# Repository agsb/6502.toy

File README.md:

# A 6502 toy

(this file is a stub)

## Introduction

_I seek for learn, not for speed._

I had an Apple II. The Furby was a two 6502 'like' toy. 

I want make a ~SBC minimal~ as my toy.

We know the Terminator’s main CPU is a 6502.

There are many "clones" [Ben Eater](https://eater.net/6502), [Mike](https://github.com/mike42/6502-computer), [Maarten](https://github.com/maarten-pennings/6502/tree/master), [Grant](http://searle.x10host.com/6502/Simple6502.html), [Álvarez](https://www.ele.uva.es/~jesus/6502copy/proto.html) and others.

And a Great support from [6502.org](http://6502.org/) forum and [Wilson Mines Co](http://wilsonminesco.com/).

This is a board for learn and testing the version for 6502 of Minimal Indirect Thread Code Forth as [IMMU](https://github.com/agsb/immu)

PS.

- [Ben Eater](https://www.youtube.com/watch?v=LnzuMJLZRdU) made a revival of 6502. 
- using ROM, for read-only memory, never changes
- using RAM, for random access memory, ever changes
- using REM, for regular eeprom memory, can changes (I2C, SPI, etc)
        
## Road Map

- make all circuit plans (W.I.P.)
- make a eeprom programmer like [Ben Eater](https://github.com/beneater/eeprom-programmer), but using arduino nano and some change in pins used.
- make a nop circuit to test cpus, using a arduino mini and [clockvar6502](https://github.com/maarten-pennings/6502/blob/master/1clock/clockvar6502)
- wire wrap the boards
          
## Hardware

### B.O.M

        - 01 x NMOS 6502 (or CMOS 65C02),
        - 01 x AT28C64, 8kb EEPROM
        - 02 x HM62256, 32kb SRAM

        - 01 x CMOS 6522, VIA Interface
        - 01 x CMOS 6551, CIA Interface

        - 02 x 74HC00, 4x2 NAND
        - 01 x 74HC04, 6x NOT
        - 01 x 74HC27, 3x3 NOR
        - 01 x 74HC10, 3x3 NAND
        - 01 x 74HC74, 2x D-FlipFlop
        - 01 x 74HC138, 3:8 DeMux

        - 08 x 3k3 Ohm, common pull-up
        - 08 x 10k0 Ohm,  weak pull-up
        - n x  0.1 uF, decoupling
        - 02 x 4.7 uF, buffer
        - 01 x crystal 1.8432 MHz,
        - 01 x  TS1813, reset delay

        - n  x color leds,
        - n  x small resistors,

        - 02 x AT24LC512, 64kb I2C EEPROM

## Topics

The 6502's default frequency of about 1 MHz is merely illustrative compared to the 3.6 GHz of current CPUs.
   
The USART is at 9600/19200 bps, 8-N-1, duplex. 

The I2C EEPROM used as permanent storage, 1 kb blocks, 64 bytes screens.
        
All devices are CMOS and 5V capable.        

Use wire wrap. 

Test NMOS-6502, CMOS-65C02,

The actual memory map will be 56k SRAM $0000-$DFFF, 8k EEPROM $E000-$FFFF and $FE00-$FEFF 256b for devices. 

The devices are mapped at $FE00 to $FEFF, reserving 16 bytes for control for each of 16 devices.

The board will have one 6551 ACIA and one (two?) 6522 VIA inside, with expansion of more devices.

Also using a 3:8 74HC138 decoder, with $0 reserved, $1 ACIA, $2 VIA, $3 VIA reserved, onboard and $4 to $7 for expansion.

A clock board by crystal of 1.8432 MHz for CIA and by 74HC74 of 0.9612 MHz for CPU.

A beat tick as NMI with 10ms delay using VIA T1 timer.

No VGA video or 101 keyboard, using terminal at USART 9600/19200 8N1, RS-232, vt-100. 

Using a LCD 16x4 by I2C, a keyboard with 6/12 keys, a beeper, a speaker and a pool of leds, for minimal use.

Using I2C and SPI protocols and devices. 

The board have two extra 8-pins DIPs slots for I2C epproms.

Use MicroChip [AARDVARK](https://onlinedocs.microchip.com/oxy/GUID-A21CD3C1-401E-4D3B-A45B-78E60737CD44-en-US-8/GUID-92136A89-CE06-46A2-8F03-80317EDD4F89.html) connector, for interface I2C and SPI

Use [UEXT](https://en.wikipedia.org/wiki/UEXT) interface for USART, I2C, SPI, 3V3, 5V0, GND

Use [65SIB](http://forum.6502.org/viewtopic.php?t=1064&start=105) for alternative interface.

Use a 64 pin connector for expansion modules.

## Software

At boot BIOS does have all functions and loads a monitor to RAM, or 

At boot, the bios will copy bytes from a I2C eeprom into RAM and jump to it.

Use a BIOS and Forth, 

Use USART for VT100 terminal, FDDI/USB for Tera-Term or PuTTy at a computer.

### Bios

Consider ram is static random memory, rom is eeprom memory and rem is flash memory

generic routines at bios:

    - ram2ram, copy bytes from RAM to RAM
    - rem2ram, copy bytes from REM to RAM
    - ram2rem, copy bytes from RAM to REM
    
    - set_spi, prepare spi
    - set_i2c, prepare i2c
    - set_sram, prepare sram page
    
    - getc, uart get a char 
    - putc, uart put a char
    
    - getcq, verify to get
    - putcq, verify to put
    
    - getp, generic port get
    - putp, generic port put
    
    - beep, as is
    - tone, play a tone
    
    - tick_put, write into counter
    - tick_get, read from counter
    - tick_run, starts counter
    - tick_hlt, stops counter
    
    - roulette, random number from 0 to 36
    - seed, random seed from 0 to $FFFF
    - random, returns a random number from 0 to $FF

    - hex2bin, convert a hexagesimal ascii to byte ($00 to $FF)
    - bin2hex, convert a byte to hexagesimal ascii ($00 to $FF)
    
## Memory 

The first 4k of RAM $0000-$0FFF is reserved for system.

The $03FF 1k reserved for system, and $E0-$FF 32 bytes at page zero. 

The Extended Wozniac Monitor uses RAM at $0200-$027F as terminal input buffer and $24-$2B at page zero. 

The page $0300-$03FF is a list of references for devices and system (BIOS, MOS) routines.

The pages $0400-$0FFF are reserved for future expansion, programs start at $1000.

The Forth uses RAM from $1000 to $DFFF, $00D0-$00DF 16 bytes at page zero and ???? to ???? at page one.

## Ideas

The hardware is 32k SRAM-1 + 32k SRAM-0 + 8k EEPROM (shadow) and devices. Two HM62256 and an AT28C64.

Usually memory banks are maped after the first 16kb. I plan use the first 32kb, $0000-$7FFF, for memory banks and the second 32kb, $8000-$FFFF for fixed memory space. This allow multiple tasks, one per bank, instantaneous context switch, without overhead of copy and swap, and shared buffers within tasks. 

Note the fixed SRAM is named SRAM-0 and hold at 0x8000 to 0xFFFF, with 256 bytes for devices and shadow the 0xE000 to 0xFFFF of EEPROM. This alllows use the A15 line as bank SRAM selector.

As reference, the Apple II memory map, uses $0000-$BFFF 48k RAM, $C000-$CFFF 4k Devices, $D000-$FFFF 12k ROM.

### Memory banks by 6522

Use 32k SRAM-1 + banks x 32k SRAM-N over 0x0000 to 0x7FFF, mapped by PB0-PB3 of 6522, + 32k SRAM-0 fixed, eeprom shadow at last 8k. Each bank is a task and fixed RAM as shared memory; 

Maybe, a module for 8 x 32k HM62256 SRAMs, selected by a 74HC138 and some control glue logics.

1. at boot both SRAM-0 and SRAM-1 onboard must be selected;
2. at boot the expansion module is not active but could be checked if plugged;
3. the bank-0 is always active, at 0x8000, selected by A15
4. a bios call does active the default bank-1, on board and disables expansion;
6. a bios call does active another 32k memory of bank-2 to bank-9 at 0x0000;

### Memory banks illegal opcodes

Use the illegal opcode 3 and B, for select SRAM BANKs of 32kb. Take SYNC, /A15, A0, A1, /A2 as selector and A3, A4, A5, A6, A7 as pseudo A15, A16, A17, A18, A19 for 32 banks of 32k, eg. two AS64008

## Modules

### Keyboard minimal

Use a ATmega328 with RST, RX, TX, GND, PWR, with a serial conector and direct conection (lines) for 16 keys switches, in split format.

### FAT32 SD 

All support for SD FAT32 borrow from [SDCARD6502](https://github.com/gfoot/sdcard6502/tree/master)

## Links

https://6502.org

http://wilsonminesco.com/

https://www.ele.uva.es/~jesus/6502copy/proto.html

https://www.youtube.com/watch?v=LrPxM-qYNTI

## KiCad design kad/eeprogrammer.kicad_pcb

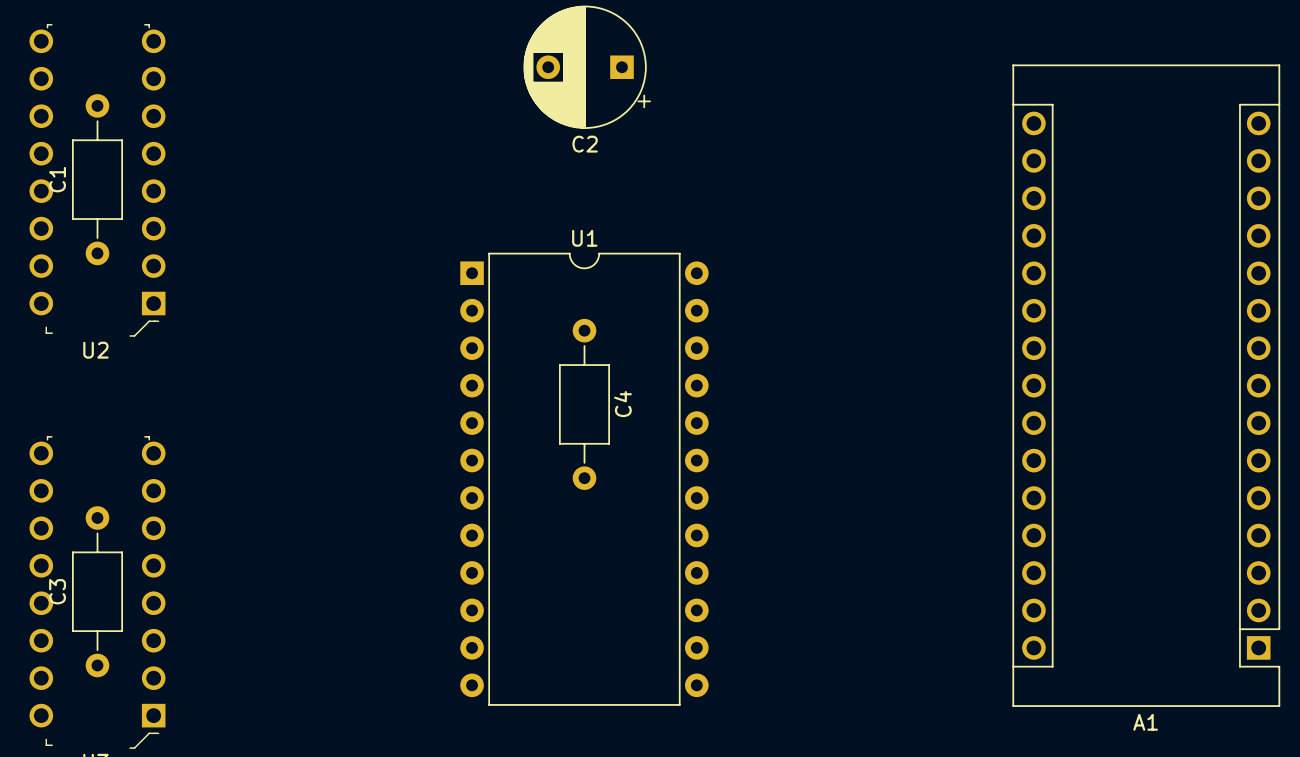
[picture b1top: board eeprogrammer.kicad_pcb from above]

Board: 2 copper layers, 8 parts (0 on the bottom side), 30 nets, no tracks yet.

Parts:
A1: Arduino_Nano_v2.x; Arduino_Nano
C1, C3, C4: C; C_Axial_L5.1mm_D3.1mm_P10.00mm_Horizontal
C2: C_Polarized; CP_Radial_D8.0mm_P5.00mm
U1: 28C16; DIP-24_W15.24mm
U2, U3: 74HC595; DIP-16_W7.62mm

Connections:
GND: A1.4 (GND), A1.29 (GND), C1.2, C2.2, C3.2, C4.2, U1.12 (GND), U2.8 (GND), U3.8 (GND)
unnamed: A1.5 (D2), U1.9 (D0)
unnamed: A1.6 (D3), U1.10 (D1)
unnamed: A1.7 (D4), U1.11 (D2)
unnamed: A1.8 (D5), U1.13 (D3)
unnamed: A1.9 (D6), U1.14 (D4)
unnamed: A1.10 (D7), U1.15 (D5)
unnamed: A1.11 (D8), U1.16 (D6)
unnamed: A1.12 (D9), U1.17 (D7)
unnamed: A1.13 (D10), U1.18 (~CS)
unnamed: A1.14 (D11), U1.20 (~OE)
unnamed: A1.15 (D12), U1.21 (~WE)
unnamed: A1.19 (A0), U2.14 (SER)
unnamed: A1.20 (A1), U2.11 (SRCLK), U3.11 (SRCLK)
unnamed: A1.21 (A2), U2.10 (~SRCLR), U3.10 (~SRCLR)
unnamed: A1.22 (A3), U2.12 (RCLK), U3.12 (RCLK)
unnamed: A1.23 (A4), U2.13 (~OE), U3.13 (~OE)
unnamed: U1.7 (A1), U2.1 (QB)
unnamed: U1.6 (A2), U2.2 (QC)
unnamed: U1.5 (A3), U2.3 (QD)
unnamed: U1.4 (A4), U2.4 (QE)
unnamed: U1.3 (A5), U2.5 (QF)
unnamed: U1.2 (A6), U2.6 (QG)
unnamed: U1.1 (A7), U2.7 (QH)
unnamed: U2.9 (QH'), U3.14 (SER)
unnamed: U1.8 (A0), U2.15 (QA)
unnamed: U1.19 (A10), U3.2 (QC)
unnamed: U1.22 (A9), U3.1 (QB)
unnamed: U1.23 (A8), U3.15 (QA)
VCC: A1.27 (+5V), C1.1, C2.1, C3.1, C4.1, U1.24 (VCC), U2.16 (VCC), U3.16 (VCC)

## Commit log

2023-09-30 easy srcs
2023-09-30 many code sources
2023-10-02 changes irq/nmi
2023-10-02 some tips for bios
2023-10-02 added quotes
2023-10-03 update quotes
2023-10-03 reviews
2023-10-04 review bios
2023-10-04 tweak bios
2023-10-05 bios adds
2023-10-05 more I2C
2023-10-06 try i2c sources, compile
2023-10-06 more I2C stuff
2023-10-06 i2c eeprom functions
2023-10-07 i2c wash
2023-10-07 i2c review
2023-10-08 clean up
2023-10-08 cleans
2023-10-09 review post
2023-10-09 randoms
2023-10-10 beepers T2 ?
2023-10-14 tune using T2/SR
2023-10-20 tunes atts
2023-10-20 clean and review
2023-10-24 acia ptrs
2023-10-27 review disclaimer and LICENSE
2023-10-31 update disclaimer
2024-11-04 more words decoded
2024-11-07 review and mor words
2024-11-08 reviews and simplify
2024-11-08 more words
2024-11-08 more easy
2024-11-09 more tweaks
2024-11-17 small changes
2024-11-20 include memory glue logic schematics
2025-03-09 minor update
2025-03-11 small reviews
2025-03-18 small updates
2025-03-23 define main
2025-03-25 small updates of references
2025-04-11 some updates
2025-04-13 added kicad eeprogrammer
2025-04-15 some changes for play
2025-04-15 update apple stuffs
2025-04-15 more snipets
2025-04-16 more snipets digital logic glues
2025-04-16 rewrite for easy
2025-04-17 rewrite boot.s
2025-04-17 new boot load
2025-04-20 does wire-wraps list sorted
2025-05-11 pagging for memory banks
2025-05-17 manuals ups
2025-05-20 plans for memory maps
2025-05-21 clean parameters
2025-05-21 clean parameters prepare for sim65 tests
2025-05-24 small changes on memory maps
2025-05-24 some memory banks ideas, still wip
2025-05-27 update kicad files
2025-05-28 updates wire wrap lists
2025-07-10 update modules
